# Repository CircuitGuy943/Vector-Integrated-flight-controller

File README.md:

I am currently trying to build my own drone from scratch, and slowly replace every component with my own, from creating fully custom PCBs for the flight controller or ESCs, to making a 3D printed drone chassis etc etc. And this is the fully fledged, multi functional, cool-looking flight controller. I present to you:

# *SABRE!*

For one of my biggest projects yet I designed a jack of all trades custom flight controller board. It also comes with custom firmware, or if possible compatibility with betaflight or other FC firmware out there. At it's core are two PCBs arranged in a stackup with the "top" and "bottom" sections. The two PCBs connect through the common 2.54mm pitch headers and stack on top of eachother and each serve to provide enough space for all the components and separate the sensitive digital components from the electromagnetic potential of the motor power rails. The bottom board houses E-Fuse protection and an INA226 current monitor to protect the boards, including powered FPV feed with the AT7456E and TX5813, accompanied by four MOSFET powered 12V LED strip channels. The top booard houses a powerful STM32F765VGT CPU which will, *fingers crossed,* be more than enough to run automatic flight levelling software quickly enough to not crash. Followed by a micro SD card slot for storing flight telemetry, programmable DIP switched for easy settings, BNO08x 9-DOF sensor module, segment display and pushbuttons for easy configuration without needing to reupload code and a BMP580 barometic sensor. More than I (or you) will ever need to fly a 4 blade, 1KG piece of PETG plastic :)

### Bottom Board:

Half of the bottom PCB houses the power delivery circuitry. This includes a dedicated TPS259850 chip, or an E-Fuse, required protection option for a drone that operates at around 20A sustained and 40A current peaks. Thanks to it's extremely low RDS on, basically no power is wasted, and it trips the circuit in a matter of microseconds when too much current is detected, which makes it extremely useful for a drone full of sensitive circuitry, compared to a traditional wire fuse. Followed by that is an INA226 chip, this aims to precisely monitor the current consumption of the entire drone, helping to predict flight times and efficiently manage battery health, through the use of a shunt resistor sized to the expected current draw. The current planes are optimized to make proper use of the different outer and inner layer thicknesses and properly distribute current with minimal heat up.

The other part of the bottom PCB houses the RF circuitry for the FPV system LED drivers togethor with power regulators that power the 12V rail for the LED drivers and the 5V rail for the FPV system and other 5V chips. The 12V power regulator (TPS55289) and the 5V regulator (TPS63070) both use the safest and most reliable layouts possible and are positioned to spatially divide the high ~32A currents on the bottom power distribution circuitry from the rest of the bottom board, a slide switch also controls the power supply to the TX5813 module, as this consumes the most out of the other board circuitry, at about ~200mA, this should help to increase flight time by cutting wasted power when the FPV function isn't being used. CSD16340 MOSFETS also serve to drive 4 seperate 12V LED strip channels, these I plan to connect to LED strips and create cool illuminations off of my drone.

The RF circuitry benefits from an impedance accurate JLC-3313 stackup and use of coplanar waveguide routing with via fencing, tearsrops and udnerpad via router to insure the least impedance mismatch possible. The actual RF system is composed of an external camera connector, or simple pin header (capable of reading almost any FPV camera such as the Caddx Ant Lite). The video signal is then passed through a meticulously routed 75ohm impedance matched trace into a MAX7456EUI (Or a newer drop in AT7456E replacement, pin to pin compatible), this module serves to inject an OSD (On screen display) into the video feed through communication with the STM32 MCU for easy sending of telemtry data like battery voltage, speed, altitude etc. The output from the OSD injection chip is then routed through another impedance matched trace with SAG correction into the video input of the TX5813. This modules handles the complicated circuitry of converting the video feed (~6MHz) into a radio signal of ~5.8GHz. That RF is then routed even more carefuly for the short length (~8mm) of the SMA launch into the SMA connector then into any respective 5.8GHz FPV antenna. (I also have a complemintary project for a 5.8GHz FPV reciever in another repository)

### Top Board:

Flying the drone is an STM32F765VGT CPU with up to 216MHz clock speed, hopefully resulting in almost perfect drone levelling and flight, on the other side of the board is also a USB C receptacle for programming the STM CPU, and powering the board while doing so (everything except the motors, of course, I also included diodes to prevent power backfeed). Close by is a BNO08x 9-DOF accelerometer, gyroscope and magnetometer, complete with an integrated 32-bit ARM Cortex-M0+ for quick sensor fusion with pre built firmware (meaning I have to code waaaay less :D). Motor PWM outputs for the ESCs also connected directly to PWM channels on the STM32 and two solder bridgeable connections to allow me to use the 5V supply from the ESCs in case my 5V regulator doesn't function properly under load (I've had bad experience with voltage regulators). Several voltage indicator LEDs are also placed near the USB C port at the back. Then there is also an UART FPC port designed to connect to a separate GPS board (large board for good GPS recieving power, check my other repositories) on the left side of the board. A 7 segment, 4 digit bitbanged display and several tactile pushbottoms also occupy the centre of the board, quite useless but they might be useful in changing more accute settings without having to reupload firmware every time. A micro SD card also connects through 4 channel SPI to STM32, I plan to use this to store settings or flight telemetry information that I could analyze while debugging. Powering all that is a 3.3V regulator (LMR51430XF), simplest (and therefore most reliable) I could find. And several other breakout headers for power/functionality. PWM inputs from the radio remote is recieved through a 3x8 header pinout designed for my specific radio reciever module.

(For BP reviewer: Btw, the two boards will be connected and bought as one piece from JLC, then I will cut them apart and stack them, I just ran out of time to do that, there's also quite a bit off polishing off to do like doing Fusion renders but I've also run out of time, so the project would be a bit more polished and it will be but not before the BP deadline. 3D file of board is also too big (over 100MB) to upload to GitHub)

## Features:
- Fully integrated design:
	- Custom firmware uploadable
	- Power distribution and control in one place
	- Dual stacked PCB design
 	- No screw, no wire inter board connection

- Power
	- Extremely low RDS protection e-Fuse (us trip time)
 	- INA226 current and voltage monitoring
  	- Backup/calibration voltage divider monitoring
  	- Fully optimized current planes, 40A+ capability
  	- Firmware built in battery management and flight warning system
  	- Meticulously designed 5V, 12V and 3.3V switching voltage regulators
  	- Backup ESC 5V supply availible
  	- LED indicators for power rail status
  	- 4 channel driver for 12V LED strips
  	- Power switch for TX5813 module for longer flight times

- Fully integrated FPV support
	- MAX7456/AT7456E OSD injection into FPV feed
	- Channel switch ability
	- TX5813 RF launch module
	- Accurate and reliable RF design
 	- Designed for impedance matched JLC 3313 stackup
 
- Flight Control
	- USB C programming connection 
	- Powerful STM32F765VGT CPU
 	- MicroSD card slot (For inflight telemtry storage)
  	- Programmable DIP switches
  	- Display/pushbuttons for setting adjustment without code reupload
  	- BNO08x 9-DOF sensor module with built in sensor fusion
  	- BMP580 Barometric sensor
  	- UART FPC connection for external GPS board
  	- Extra power and I2C debug headers
  	- 7 input PWM channels
  	- 4 ESC output PWM channels

## PCB
This is the PCB, with L1 to L4 Layers, silkscreen for both layers and an all layers view

And here is the schematic

## 3D render
Here is also a 3D render to show off the PCB :)

## Firmware Overview
I've included some basic firmware (**untested**) that should get the TFT display working out of the box with a quick upload from arduino IDE

## BOM:
The BOM list for the actual PCB components is in the BOM folder section and here is also a BOM list for all the other components I plan to buy for this:

- PCB             $378.08		
- Antenna         $7.77      https://www.aliexpress.com/item/1005006153683653.html		
- 90 degree SMA   $4.51      https://www.aliexpress.com/item/1005005665998117.html						
- TX5813 module   $15.82     https://www.aliexpress.com/item/1005011698073364.html
											
Total			      $406.18

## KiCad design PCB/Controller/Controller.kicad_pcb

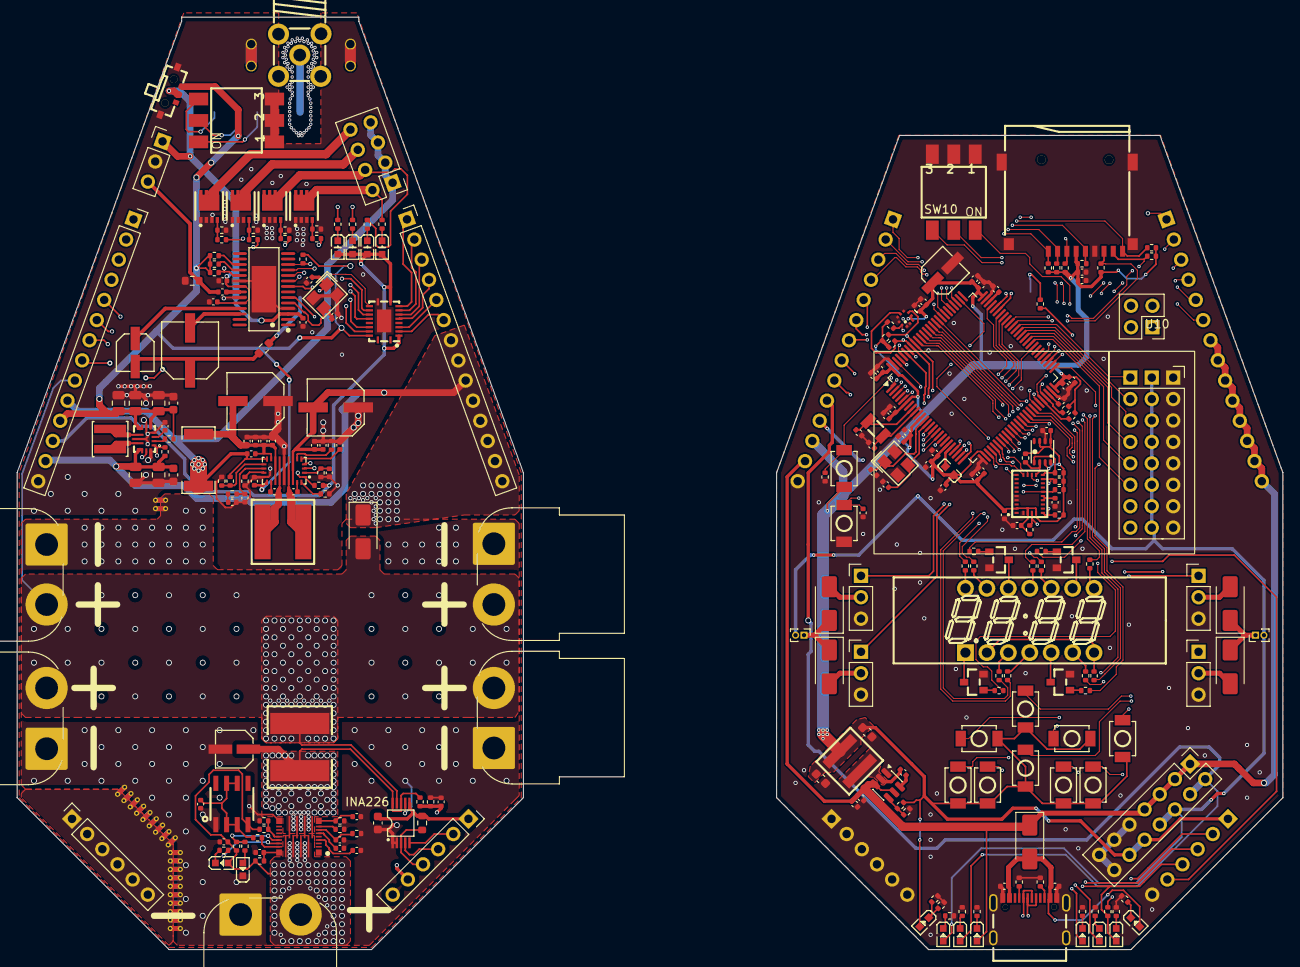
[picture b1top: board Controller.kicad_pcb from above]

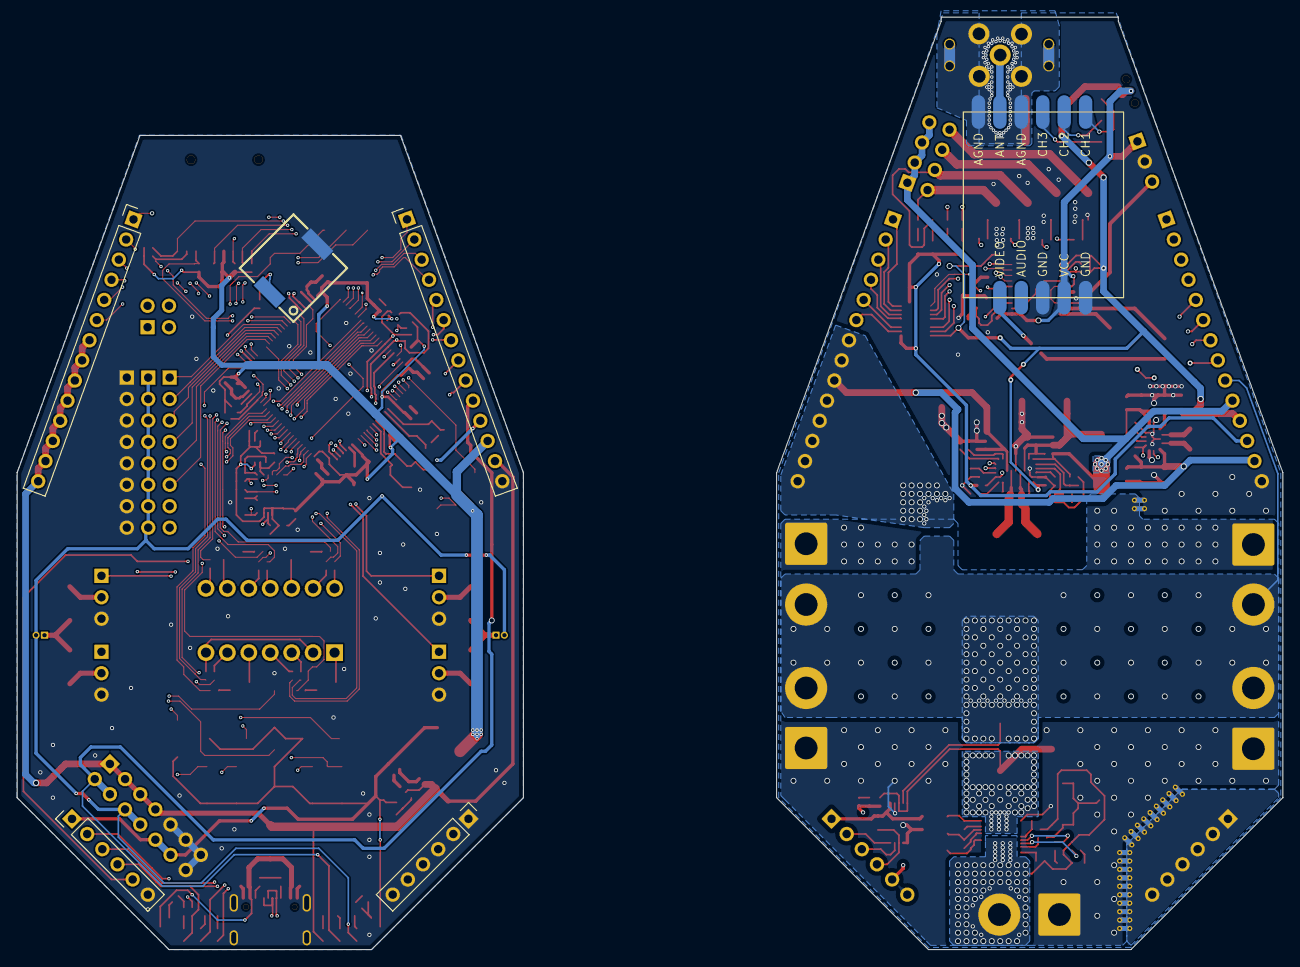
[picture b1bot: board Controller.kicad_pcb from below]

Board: 4 copper layers, 150.0 x 110.5 mm, 284 parts (6 on the bottom side), 219 nets.

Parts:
BUZ1: CPT-9019S-SMT-TR; BUZ-SMD_L9.0-W9.0-P8.00-LS9.3
C1: 0.1uF; C_0603_1608Metric
C2, C11, C14, C15, C26, C27, C29, C30, C31, C32, C33, C34, C36, C37, C38, C41, C44, C45, C46, C47, C48, C49, C50, C51, C63, C64, C67, C78: 100nF; C_0402_1005Metric
C3, C6: 10uF; C_0603_1608Metric
C4, C5: 10uF; C_0805_2012Metric
C7, C8, C9: 22uF; C_0805_2012Metric
C10, C57, C58: 2.2uF; C_0402_1005Metric
C12, C13: 22uF; C_0603_1608Metric
C16, C19, C20, C21, C22: 22uF; C_0402_1005Metric
C17: 4.7uF; C_0402_1005Metric
C18, C28: 22nF; C_0402_1005Metric
C23: 3300pF; C_0402_1005Metric
C24: 330pF; C_0402_1005Metric
C25: 47uF; CAP-SMD_BD6.3-L6.6-W6.6-LS7.2-FD
C35, C43, C56, C68, C77: 10uF; C_0402_1005Metric
C39, C40, C60, C61: 20pF; C_0402_1005Metric
C42, C66, C74: RVT1C220M0405_C3356_22uF; CAP-SMD_BD4.0-L4.3-W4.3-FD-LS5.3
C52, C53, C54, C55, C65: 1uF; C_0402_1005Metric
C59, C62: 6.8pF; C_0402_1005Metric
C69, C75, C76: 0.1uF; C_0402_1005Metric
C70: 15nF; C_0402_1005Metric
C71: 3.3nF; C_0402_1005Metric
C72: 10nF; C_0402_1005Metric
C73: 150pF; C_0402_1005Metric
CN1: XT60PW_M; AMASS_XT60PW-M_1x02_P7.20mm_Horizontal
CN2, CN4, CN5, CN6: XT60PW_F; AMASS_XT60PW-F_1x02_P7.20mm_Horizontal
Card2: TF-01A; TF-SMD_TF-01A
D1, D2, D3, D4, D5, D6: SS34; D_SMA
J1: Conn_02x07_Odd_Even; PinHeader_2x07_P2.54mm_Vertical
J2, J9: Conn_01x02_Pin; PinHeader_1x02_P1.00mm_Vertical
J5, J6, J7, J8, J10: Conn_01x03_Pin; PinHeader_1x03_P2.54mm_Vertical
J12: Conn_02x02_Top_Bottom; PinHeader_2x02_P2.54mm_Vertical
J13, J18: Conn_01x14_Pin; PinHeader_1x14_P2.54mm_Vertical
J14, J19: Conn_01x06_Pin; PinHeader_1x06_P2.54mm_Vertical
J15, J20: Conn_01x14_Socket; PinSocket_1x14_P2.54mm_Vertical
J16, J17: Conn_01x06_Socket; PinSocket_1x06_P2.54mm_Vertical
J21: Conn_02x04_Odd_Even; PinHeader_2x04_P2.54mm_Vertical
L1: XFL4020-152MEC; IND-SMD_L4.0-W4.0-A
L2: FCM1608KF-601T03; L0603
LED1: FJ2481CH; LED-SEG-TH_14P-L32.2-W10.2-P2.54-S7.62-BL
LED2, LED9, LED11, LED12, LED13, LED14, LED15, LED16: KT-0603YG; LED0603-RD
LED3, LED8: KT-0603R; LED0603-RD
LED4, LED5, LED6, LED7: KT-0603W; LED0603-R-RD_WHITE
NT1, NT7, NT8, NT9, NT10, NT10#2, NT10#3, NT10#4, NT11, NT11#2, NT11#3, NT11#4, NT12, NT13, NT13#2, NT13#3, NT14, NT15, NT15#2, NT15#3, NT16: NetTie_2; NetTie-2_THT_Pad0.3mm
NT2, NT17: NetTie_2; NetTie-2_THT_Pad1.0mm
Q1, Q2, Q3, Q5: CSD16340Q3; VSON-CLIP-8_L3.3-W3.3-P0.65-BL
Q7, Q8, Q9, Q10: LBSS138LT1G; SOT-23_L2.9-W1.3-P1.90-LS2.4-BR
R1, R2: 5.1K; R_0402_1005Metric
R3: HOLR2725D-4W-2MR-1%; R2725
R4, R17, R18, R19, R21, R36, R37, R38, R39, R40, R41, R42, R43, R44, R45, R46, R47, R48, R60, R67, R68, R69, R76, R77, R82: 220; R_0402_1005Metric
R5, R72, R73, R74, R75: 680; R_0402_1005Metric
R6, R7, R12, R20, R22, R27, R28, R29, R30, R31, R34, R35, R49, R58, R61, R62, R63, R64, R65, R66, R88, R96, R97, R98, R102: 10K; R_0402_1005Metric
R8, R9: 100K; R_0402_1005Metric
R10: 22.1K; R_0402_1005Metric
R11, R33: 68K; R_0402_1005Metric
R13, R14: 56K; R_0402_1005Metric
R15: MS122WF100MT4E; R2512
R16, R99, R100, R103, R104: 4.7K; R_0402_1005Metric
R23: 150K; R_0402_1005Metric
R24: 47K; R_0402_1005Metric
R25, R26, R55: 2.2K; R_0402_1005Metric
R32, R54, R85, R86, R87: 1K; R_0402_1005Metric
R50: 160; R_0402_1005Metric
R51: 1.1K; R_0402_1005Metric
R52: 48K; R_0402_1005Metric
R53: 1.5K; R_0402_1005Metric
R56: 50K; R_0402_1005Metric
R78: 100; R_0402_1005Metric
R83, R84: 75; R_0603_1608Metric
R101: 10K; R_0603_1608Metric
SW1, SW2, SW3, SW4, SW5, SW6, SW7, SW8, SW9, SW11, SW12: TS-1088-AR02016; SW-SMD_L3.9-W3.0-P4.45
SW10, SW14: DSIC03LSGET; SW-SMD_DSIC03LSGET
SW13: MK-11C04-G013; SW-SMD_MK-11C04-G013
U1: STM32F765VGTx; LQFP-100_14x14mm_P0.5mm
U2: BNO080; LGA-28_L5.2-W3.8-P0.50-BL-1
U3: BMP580; LGA-10_L2.0-W2.0-P0.50-TL_BMP580
U4: XAL5050-562MEC; IND-SMD_L5.5-W5.3
U5: MAX7456EUI; HTSSOP-28_L9.7-W4.4-P0.65-LS6.4-BL-EP5.5
U6: SMA_Conn; SMA-TH_SMA-KWE_C7498154
U7: TPS55289RYQR; VQFN-21_L5.0-W3.0-P0.50-TL
U8: XAL7070-472MEC; IND-SMD_L7.5-W7.2-1
U9: TPS630701RNMT; VQFN-15_L3.0-W2.5-P0.50-BL
U10: MC7RE
U11: INA226AQDGSRQ1; VSSOP-10_L3.0-W3.0-P0.50-LS4.9-BL
U12: LMR51430; SOT-23-6
U13, U18: 100uF; CAP-SMD_BD6.3-L6.6-W6.6-LS7.2-FD-1
U14: BME280; LGA-8_BME280_BL
U15: S322527M20PF10PPM; CRYSTAL-SMD_4P-L3.2-W2.5-BL
U16: TXB0108RGYR; VQFN-20_L4.5-W3.5-P0.50-BL-EP
U17: TX5813
U19: TPS259850RQPR; QFN-26_L5.0-W4.5_TPS259850RQPR
U20: LD1117D33TR; SO-8_L4.9-W3.9-P1.27-LS6.0-BL
USB1: TYPE-C 16P(073); USB-C-SMD_TYPE-C16PIN_C668624
X1: X322525MOB4SI; CRYSTAL-SMD_4P-L3.2-W2.5-BL
X2: Q13FC1350000400; FC-135R_L3.2-W1.5

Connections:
+3.3V: C12.2, C13.2, C29.1, C30.1, C32.2, C33.2, C34.2, C42.1, C43.1, C45.1, C46.1, C47.1, C48.1, C49.1, C50.1, C51.1, C52.1, C53.1, C54.1, C55.1, C56.1, C64.1, C65.1, C67.1, C68.1, Card2.4 (VDD), J1.10, J1.12, J13.12, J14.1, L2.2, LED16.2 (A), R6.2, R9.2, R25.2, R26.2, R27.1, R58.2, R61.2, R62.2, R63.2, R64.2, R65.2, R66.2, R96.1, R97.1, R98.1, R99.1, R100.1, R102.1, R103.2, R104.2, SW1.2, SW2.2, SW3.2, SW4.2, SW5.2, SW6.2, SW7.2, SW8.2, SW9.2, SW12.1, U1.6 (VBAT), U1.11 (VDD), U1.20 (VREF+), U1.27 (VDD), U1.50 (VDD), U1.75 (VDD), U1.100 (VDD), U2.3 (VDD), U2.5 (PS1), U2.28 (VDDIO), U3.1 (VDDIO), U3.10 (VDD), U4.2, U14.2 (CSB), U14.6 (VDDIO), U14.8 (VDD)
+3.3V_B: C1.2, J15.12, J16.1, LED4.1 (A), LED5.1 (A), LED6.1 (A), LED7.1 (A), R28.1, R101.2, U11.6 (VS+), U16.2 (VCCA), U16.10 (OE)
+5V: J1.6, J1.8, J2.2, J9.2, J13.11, LED15.2 (A), U10.17 (5V), U10.18 (5V), U10.19 (5V), U10.20 (5V), U10.21 (5V), U10.22 (5V), U10.23 (5V), U10.24 (SBUS3)
+5V_B: C6.2, C7.2, C8.2, C9.2, C17.2, J15.11, R8.2, R85.2, R86.2, R87.2, R88.2, SW13.1, U7.18 (VCC), U9.5 (FB), U9.7 (VOUT), U16.19 (VCCB)
+12V: J1.2, J1.4, J13.10, LED14.2 (A)
+12V_B: C26.1, J15.10, J21.1, J21.3, J21.5, J21.7, R11.2, R15.2, U7.13 (ISN)
BMP580_INT: R102.2, U1.96 (PB9), U3.7 (INT)
BNO580_BOOTN: R27.2, U1.34 (PB0), U2.4 (BOOTN)
BNO580_CSN: U1.77 (PA15), U2.18 (H_CSN)
BNO580_INTN: R98.2, U1.33 (PC5), U2.14 (H_INTN)
BNO580_MISO: U1.30 (PA6), U2.20 (H_SDA/H_MISO/TX)
BNO580_MOSI: U1.31 (PA7), U2.17 (SA0/H_MOSI)
BNO580_NRST: R97.2, U1.32 (PC4), U2.11 (NRST)
BNO580_SCLK: U1.29 (PA5), U2.19 (H_SCL/SCK/RX)
BNO580_WAKE: R96.2, U1.35 (PB1), U2.6 (PS0/WAKE)
BOOT: R22.1, SW12.2, U1.94 (BOOT0)
BOOT1: C14.2, U7.8 (SW1), U8.2
BOOT2: C15.2, U7.10 (SW2), U8.1
BUTTON_DECREASE: SW4.1, U1.39 (PE9)
BUTTON_F1: SW6.1, U1.41 (PE11)
BUTTON_F2: SW7.1, U1.42 (PE12)
BUTTON_F3: SW8.1, U1.43 (PE13)
BUTTON_F4: SW9.1, U1.51 (PB12)
BUTTON_INCREASE: SW3.1, U1.38 (PE8)
BUTTON_LEFT: SW1.1, U1.36 (PB2)
BUTTON_OK: SW5.1, U1.40 (PE10)
BUTTON_RIGHT: SW2.1, U1.37 (PE7)
BUZZER: R78.1, U1.53 (PB14)
DIP_1: SW10.6 (B1), U1.52 (PB13)
DIP_2: SW10.5 (B2), U1.54 (PB15)
DIP_3: SW10.4 (B3), U1.55 (PD8)
DISP_A: R41.2, U1.87 (PD6)
DISP_B: R44.2, U1.86 (PD5)
DISP_C: R38.2, U1.85 (PD4)
DISP_D: R39.2, U1.84 (PD3)
DISP_D2D1: R45.2, U1.58 (PD11)
DISP_DIG1: R46.1, U1.91 (PB5)
DISP_DIG2: R48.1, U1.90 (PB4)
DISP_DIG3: R36.1, U1.89 (PB3)
DISP_DIG4: R47.1, U1.88 (PD7)
DISP_DP: R40.2, U1.67 (PA8)
DISP_E: R37.2, U1.72 (PA13)
DISP_F: R42.2, U1.69 (PA10)
DISP_G: R43.2, U1.68 (PA9)
EXTRA_I2C_EN: J12.4, U1.44 (PE14)
EXTRA_I2C_INT: J12.3, U1.45 (PE15)
EXTRA_I2C_SCL: J12.1, R103.1, U1.46 (PB10)
EXTRA_I2C_SDA: J12.2, R104.1, U1.47 (PB11)
GND: BUZ1.2 (-), C10.2, C12.1, C13.1, C29.2, C30.2, C31.1, C32.1, C33.1, C34.1, C35.2, C42.2, C43.2, C45.2, C46.2, C47.2, C48.2, C49.2, C50.2, C51.2, C52.2, C53.2, C54.2, C55.2, C56.2, C57.1, C58.1, C59.2, C60.2, C61.1, C62.2, C63.2, C64.2, C65.2, C67.2, C68.2, C77.2, C78.2, Card2.6 (VSS), Card2.10 (GND), Card2.11 (GND), Card2.12 (GND), Card2.13 (GND), J1.9, J1.11, J1.13, J1.14, J5.3, J6.3, J7.3, J8.3, J13.14, J14.6, J19.1, J19.2, J19.3, J19.4, J19.5, J19.6, Q7.2 (S), Q8.2 (S), Q9.2 (S), Q10.2 (S), R1.2, R2.2, R4.2, R5.2, R10.2, R22.2, R72.2, R73.2, R74.2, R75.2, R76.2, R77.2, R82.2, SW10.1 (A1), SW10.2 (A2), SW10.3 (A3), SW11.1, U1.10 (VSS), U1.19 (VSSA), U1.26 (VSS), U1.49 (VSS), U1.74 (VSS), U1.99 (VSS), U2.2 (GND), U2.25 (GND), U2.26 (XOUT32/CLKSEL1), U3.3 (VSS), U3.5 (SDO), U3.6 (CSB), U3.8 (VSS), U3.9 (VSS), U10.9 (GND), U10.10 (GND), U10.11 (GND), U10.12 (GND), U10.13 (GND), U10.14 (GND), U10.15 (GND), U10.16 (SBUS2), U12.1 (GND), U14.1 (GND), U14.7 (GND), USB1.1 (SHELL), USB1.2 (SHELL), USB1.3 (SHELL), USB1.4 (SHELL), USB1.A1B12 (GND), USB1.B1A12 (GND), X1.2 (GND), X1.4 (GND)
GND_B: C2.2, C3.1, C4.1, C5.1, C6.1, C7.1, C8.1, C9.1, C16.1, C17.1, C18.1, C19.1, C20.1, C21.1, C22.1, C23.1, C24.1, C25.1, C27.1, C36.1, C37.1, C38.1, C39.2, C40.1, C44.2, J10.2, J15.14, J16.6, J17.1, J17.2, J17.3, J17.4, J17.5, J17.6, NT1.1, NT2.2, NT7.1, NT8.1, NT9.1, NT10.1, NT10#2.1, NT10#3.1, NT10#4.1, NT11.1, NT11#2.1, NT11#3.1, NT11#4.1, NT12.1, NT13.1, NT13#2.1, NT13#3.1, NT14.1, NT15.1, NT15#2.1, NT15#3.1, NT16.1, NT17.2, Q1.1 (S), Q1.2 (S), Q1.3 (S), Q2.1 (S), Q2.2 (S), Q2.3 (S), Q3.1 (S), Q3.2 (S), Q3.3 (S), Q5.1 (S), Q5.2 (S), Q5.3 (S), R13.1, R14.2, R16.1, R20.2, R29.1, R30.1, R31.1, R34.1, R35.1, R83.2, SW13.4, SW13.5, SW14.1 (A1), SW14.2 (A2), SW14.3 (A3), U5.4 (DGND), U5.20 (AGND), U5.23 (PGND), U5.29 (EP), U7.9 (PGND), U7.17 (AGND), U9.4 (GND), U9.6 (FB2), U9.10 (PGND), U9.15 (VSEL), U13.1, U15.2 (GND), U15.4 (GND), U16.11 (GND), U16.21 (EP), U17.9 (GND), U17.11 (GND)
HSE_IN: C61.2, U1.12 (PH0), X1.1 (OSC1)
HSE_OUT: C60.1, U1.13 (PH1), X1.3 (OSC2)
INA_ALERT_B: J16.4, R101.1, U11.3 (Alert)
INA_ALERT_T: J14.4, LED3.2 (A), R6.1, U1.95 (PB8)
LED1_POWER: J21.8, Q1.5 (D), Q1.6 (D), Q1.7 (D), Q1.8 (D), R67.2
LED1_PWM_B: J15.1, R17.2
LED1_PWM_T: J13.1, U1.15 (PC0)
LED2_POWER: J21.6, Q2.5 (D), Q2.6 (D), Q2.7 (D), Q2.8 (D), R60.2
LED2_PWM_B: J15.2, R18.2
LED2_PWM_T: J13.2, U1.16 (PC1)
LED3_POWER: J21.4, Q5.5 (D), Q5.6 (D), Q5.7 (D), Q5.8 (D), R68.2
LED3_PWM_B: J15.3, R21.2
LED3_PWM_T: J13.3, U1.17 (PC2)
LED4_POWER: J21.2, Q3.5 (D), Q3.6 (D), Q3.7 (D), Q3.8 (D), R69.2
LED4_PWM_B: J15.4, R19.2
LED4_PWM_T: J13.4, U1.18 (PC3)
LSE_IN: C59.1, U1.8 (PC14), X2.1
LSE_OUT: C62.1, U1.9 (PC15), X2.2
MAIN_SCK_B: J15.6, J16.2, U7.3 (SCL), U11.5 (SCL)
MAIN_SCK_T: J13.6, J14.2, R99.2, U1.92 (PB6), U3.2 (SCK)
MAIN_SDA_B: J15.7, J16.3, U7.4 (SDA), U11.4 (SDA)
MAIN_SDA_T: J13.7, J14.3, R100.2, U1.93 (PB7), U3.4 (SDI)
MAX7456_CS_3.3V_B: J20.4, U16.6 (A5)
MAX7456_CS_3.3V_T: J18.4, U1.3 (PE4)
MAX7456_CS_5V: U5.8 (~CS), U16.15 (B5)
MAX7456_HSYNC_5V: R87.1, U5.18 (~HSYNC)
MAX7456_LOS_3.3V_B: J20.5, U16.4 (A3)
MAX7456_LOS_3.3V_T: J18.5, U1.2 (PE3)
MAX7456_LOS_5V: R86.1, U5.12 (LOS), U16.17 (B3)
MAX7456_RESET_3.3V_B: J20.6, U16.3 (A2)
MAX7456_RESET_3.3V_T: J18.6, U1.98 (PE1)
MAX7456_RESET_5V: R88.1, U5.19 (~RESET), U16.18 (B2)
MAX7456_SCLK_3.3V_B: J20.1, U16.9 (A8)
MAX7456_SCLK_3.3V_T: J18.1, U1.1 (PE2)
MAX7456_SCLK_5V: U5.10 (SCLK), U16.12 (B8)
MAX7456_SDIN_3.3V_B: J20.2, U16.8 (A7)
MAX7456_SDIN_3.3V_T: J18.2, U1.5 (PE6)
MAX7456_SDIN_5V: U5.9 (SDIN), U16.13 (B7)
MAX7456_SDOUT_3.3V_B: J20.3, U16.7 (A6)
MAX7456_SDOUT_3.3V_T: J18.3, U1.4 (PE5)
MAX7456_SDOUT_5V: U5.11 (SDOUT), U16.14 (B6)
MAX7456_VSYNC_5V: R85.1, U5.17 (~VSYNC)
MGND_B: C1.1, C28.1, C69.1, C70.2, C71.2, C72.1, C73.1, C74.2, C75.1, C76.2, CN1.1 (-), CN2.2, CN4.2, CN5.2, CN6.2, LED9.1 (K), NT1.2, NT7.2, NT8.2, NT9.2, NT10.2, NT10#2.2, NT10#3.2, NT10#4.2, NT11.2, NT11#2.2, NT11#3.2, NT11#4.2, NT12.2, NT13.2, NT13#2.2, NT13#3.2, NT14.2, NT15.2, NT15#2.2, NT15#3.2, NT16.2, R24.2, R49.1, R50.1, R51.2, R52.2, U11.1 (A1), U11.2 (A0), U11.7 (GND), U19.14 (GND), U20.1 (ADJ/GND)
MOTOR_PWM1: J5.1, U1.22 (PA0)
MOTOR_PWM2: J6.1, U1.23 (PA1)
MOTOR_PWM3: J7.1, U1.24 (PA2)
MOTOR_PWM4: J8.1, U1.25 (PA3)
unnamed: BUZ1.1 (+), R78.2
unnamed: C24.2, R12.1
unnamed: C66.2, R84.2, U18.1
unnamed: C76.1, R56.1, U20.2 (VOUT), U20.3 (VOUT), U20.6 (VOUT), U20.7 (VOUT)
unnamed: C75.2, CN1.2 (+), LED8.2 (A), R32.2, R33.2, R55.1, U19.23 (VIN), U19.24 (VIN), U19.25 (VIN), U19.26 (VIN), U20.4 (VIN)
unnamed: D3.2 (A), J5.2
unnamed: D3.1 (K), D4.1 (K), J2.1
unnamed: D4.2 (A), J6.2
unnamed: D5.2 (A), J7.2
unnamed: D5.1 (K), D6.1 (K), J9.1
unnamed: D6.2 (A), J8.2
unnamed: LED1.14 (A), R42.1
unnamed: LED1.8 (B), R44.1
unnamed: LED1.6 (C), R38.1
unnamed: LED1.11 (D2D1), R41.1
unnamed: LED1.2 (D), LED1.7 (D), R39.1
unnamed: LED1.1 (DIG1), Q7.3 (D)
unnamed: LED1.12 (DIG2), Q10.3 (D)
unnamed: LED1.5 (DIG3), Q8.3 (D)
unnamed: LED1.9 (DIG4), Q9.3 (D)
unnamed: LED1.3 (DP), R40.1
unnamed: LED1.4 (E), R37.1
unnamed: LED1.13 (F), R45.1
unnamed: LED1.10 (G), R43.1
unnamed: LED2.1 (K), R72.1
unnamed: LED3.1 (K), R4.1
unnamed: LED4.2 (K), R67.1
unnamed: LED5.2 (K), R60.1
unnamed: LED6.2 (K), R68.1
unnamed: LED7.2 (K), R69.1
unnamed: LED8.1 (K), R53.1
unnamed: LED9.2 (A), R54.1
unnamed: LED11.1 (K), R5.1
unnamed: LED12.1 (K), R73.1
unnamed: LED13.1 (K), R74.1
unnamed: LED14.1 (K), R75.1
unnamed: LED15.1 (K), R76.1
unnamed: LED16.1 (K), R77.1, R82.1
unnamed: NT2.1, NT17.1, U6.1, U6.2, U6.3, U6.4, U17.1 (AGND), U17.3 (AGND)
unnamed: Q1.4 (G), R17.1, R29.2
unnamed: Q2.4 (G), R18.1, R30.2
unnamed: Q3.4 (G), R19.1, R34.2
unnamed: Q5.4 (G), R21.1, R31.2
unnamed: Q7.1 (G), R46.2
unnamed: Q8.1 (G), R36.2
unnamed: Q9.1 (G), R47.2
unnamed: Q10.1 (G), R48.2
unnamed: C57.2, U1.48 (VCAP_1)
unnamed: C58.2, U1.73 (VCAP_2)
unnamed: L2.1, U1.21 (VDDA)
unnamed: C31.2, U2.9 (CAP), U2.10 (CLKSEL0)
unnamed: C66.1, U5.25 (SAG)
unnamed: C41.2, U5.22 (VIN)
unnamed: U5.26 (VOUT), U18.2
unnamed: C14.1, U7.20 (BOOT1)
unnamed: C15.1, U7.19 (BOOT2)
unnamed: R13.2, U7.16 (CDC)
unnamed: C23.2, R12.2, U7.15 (COMP)
unnamed: C18.2, U7.5 (DITH/SYNC)
unnamed: R20.1, U7.21 (EXTVCC)
unnamed: R11.1, R16.2, U7.14 (FB/~INT)
unnamed: R14.1, U7.6 (FSW)
unnamed: C19.2, C20.2, C21.2, C22.2, C25.2, C26.2, R15.1, U7.11 (VOUT), U7.12 (ISP)
unnamed: C44.1, R35.2, U7.2 (MODE)
unnamed: R7.2, U9.1 (PS/S), U9.14 (EN)
unnamed: L1.1, U9.11 (L1)
unnamed: L1.2, U9.9 (L2)
unnamed: R8.1, U9.2 (PG)
unnamed: C2.1, U9.3 (VAUX)
unnamed: C11.1, U12.6 (CB)
unnamed: R9.1, R10.1, U12.4 (FB)
unnamed: C11.2, U4.1, U12.2 (SW)
unnamed: R26.1, U2.15 (ENV_SCL), U14.4 (SCK)
unnamed: R25.1, U2.16 (ENV_SDA), U14.3 (SDI)
unnamed: U6.5, U17.2 (ANT)
unnamed: C71.1, U19.4 (DVDT)
unnamed: R33.1, R49.2, U19.18 (EN/UVLO)
unnamed: R50.2, U19.8 (ILIM)
unnamed: C72.2, R51.1, U19.7 (IMON)
unnamed: C73.2, R52.1, U19.9 (IREF)
unnamed: C70.1, U19.6 (ITIMER)
unnamed: R54.2, R55.2, U19.19 (PG)
unnamed: R56.2, U19.21 (SWEN)
unnamed: C69.2, R32.1, U19.22 (VDD)
unnamed: R53.2, U19.20 (~FLT)
unnamed: R2.1, USB1.A5 (CC1)
unnamed: R1.1, USB1.B5 (CC2)
RADIO_PWM1: U1.64 (PC7), U10.1 (CH1)
RADIO_PWM2: U1.63 (PC6), U10.2 (CH2)
RADIO_PWM3: U1.62 (PD15), U10.3 (CH3)
RADIO_PWM4: U1.61 (PD14), U10.4 (CH4)
RADIO_PWM5: U1.60 (PD13), U10.5 (CH5)
RADIO_PWM6: U1.59 (PD12), U10.6 (CH6)
RESET: C63.1, SW11.2, U1.14 (NRST)
SD_CD: Card2.9 (CD), R58.1, U1.82 (PD1)
SD_CLK: Card2.5 (CLK(SCLK)), R64.1, U1.80 (PC12)
SD_CMD: Card2.3 (CMD(DI)), R65.1, U1.83 (PD2)
SD_DAT0: Card2.7 (DAT0(D0)), R63.1, U1.65 (PC8)
SD_DAT1: Card2.8 (DAT1(RSV)), R62.1, U1.66 (PC9)
SD_DAT2: Card2.1 (DAT2(RSV)), R61.1, U1.78 (PC10)
SD_DAT3: Card2.2 (CDDAT3(CS)), R66.1, U1.79 (PC11)
TPS_ENABLE_B: J15.5, R28.2, U7.1 (EN/UVLO)
TPS_ENABLE_T: J13.5, U1.97 (PE0)
USB_DN: U1.70 (PA11), USB1.A7 (DN1), USB1.B7 (DN2)
USB_DP: U1.71 (PA12), USB1.A6 (DP1), USB1.B6 (DP2)
VBAT: J13.8, LED11.2 (A)
VBAT_B: C74.1, J15.8, R3.2, R23.1, U11.8 (VBUS), U11.10 (VIN+), U19.10 (VOUT), U19.11 (VOUT), U19.12 (VOUT), U19.13 (VOUT)
VBUS: C35.1, C77.1, D1.2 (A), LED2.2 (A), USB1.A4B9 (VBUS), USB1.B4A9 (VBUS)
VIDEO_IN: C41.1, J10.3, R83.1
VIDEO_OUT: R84.1, U17.7 (VIDEO)
VMOTORS: J13.9, LED12.2 (A)
VMOTORS_B: CN2.1, CN4.1, CN5.1, CN6.1, D2.2 (A), J15.9, R3.1, U11.9 (VIN-)
VOLTAGE_ADC_B: C28.2, J16.5, R23.2, R24.1
VOLTAGE_ADC_T: J14.5, U1.28 (PA4)
VSYS: C10.1, C78.1, D1.1 (K), J1.1, J1.3, J1.5, J1.7, J13.13, J18.7, J18.8, J18.9, J18.10, J18.11, J18.12, J18.13, J18.14, LED13.2 (A), U12.3 (VIN), U12.5 (EN)
VSYS_B: C3.2, C4.2, C5.2, C16.2, C27.2, D2.1 (K), J15.13, J20.7, J20.8, J20.9, J20.10, J20.11, J20.12, J20.13, J20.14, R7.1, U7.7 (VIN), U9.12 (VIN), U13.2
VTX_CH1: SW14.4 (B3), U17.6 (CH1)
VTX_CH2: SW14.5 (B2), U17.5 (CH2)
VTX_CH3: SW14.6 (B1), U17.4 (CH3)
VTX_SUPPLY: C36.2, C37.2, C38.2, J10.1, SW13.C, U5.3 (DVDD), U5.21 (AVDD), U5.24 (PVDD), U17.10 (VCC)
XTAL1: C40.2, U5.5 (CLKIN), U15.3
XTAL2: C39.1, U5.6 (XFB), U15.1

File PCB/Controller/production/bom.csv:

Designator,Footprint,Quantity,Value,LCSC Part #
BUZ1,BUZ-SMD_L9.0-W9.0-P8.00-LS9.3,1,CPT-9019S-SMT-TR,C95163
C1,0603,1,0.1uF,
"C10, C57, C58",0402,3,2.2uF,
"C11, C14, C15, C2, C27, C29, C30, C31, C32, C33, C34, C36, C37, C38, C41, C44, C45, C46, C47, C48, C49, C50, C51, C63, C64, C67, C78",0402,27,100nF,
"C12, C13",0603,2,22uF,
"C16, C19, C20, C21, C22",0402,5,22uF,
C17,0402,1,4.7uF,
"C18, C28",0402,2,22nF,
C23,0402,1,3300pF,
C24,0402,1,330pF,
C25,CAP-SMD_BD6.3-L6.6-W6.6-LS7.2-FD,1,47uF,C970677
"C3, C6",0603,2,10uF,
"C35, C43, C56, C68, C77",0402,5,10uF,
"C39, C40, C60, C61",0402,4,20pF,
"C4, C5",0805,2,10uF,
"C42, C74",CAP-SMD_BD4.0-L4.3-W4.3-FD-LS5.3,2,RVT1C220M0405_C3356_22uF,C3356
"C52, C53, C54, C55, C65",0402,5,1uF,
"C59, C62",0402,2,6.8pF,
C66,1210,1,100uF,
"C69, C75, C76",0402,3,0.1uF,
"C7, C8, C9",0805,3,22uF,
C70,0402,1,15nF,
C71,0402,1,3.3nF,
C72,0402,1,10nF,
C73,0402,1,150pF,
C79,1206,1,22uF,
CARD2,TF-SMD_TF-01A,1,TF-01A,C91145
CN1,AMASS_XT60PW-M_1x02_P7.20mm_Horizontal,1,XT60PW_M,C98732
"CN2, CN4, CN5, CN6",AMASS_XT60PW-F_1x02_P7.20mm_Horizontal,4,XT60PW_F,C428722
"D1, D2, D3, D4, D5, D6",D_SMA,6,SS34,
GPS,FPC-SMD_6P-P0.50_XUNPU_FPC-05F-6PH20,1,FPC-05F-6PH20,C2856796
J1,PinHeader_2x07_P2.54mm_Vertical,1,Conn_02x07_Odd_Even,
"J10, J5, J6, J7, J8",PinHeader_1x03_P2.54mm_Vertical,5,Conn_01x03_Pin,
J12,PinHeader_2x02_P2.54mm_Vertical,1,Conn_02x02_Top_Bottom,
"J13, J18",PinHeader_1x14_P2.54mm_Vertical,2,Conn_01x14_Pin,
"J14, J19",PinHeader_1x06_P2.54mm_Vertical,2,Conn_01x06_Pin,
"J15, J20",PinSocket_1x14_P2.54mm_Vertical,2,Conn_01x14_Socket,
"J16, J17",PinSocket_1x06_P2.54mm_Vertical,2,Conn_01x06_Socket,
"J2, J9",PinHeader_1x02_P1.00mm_Vertical,2,Conn_01x02_Pin,
J21,PinHeader_2x04_P2.54mm_Vertical,1,Conn_02x04_Odd_Even,
L1,IND-SMD_L4.0-W4.0-A,1,XFL4020-152MEC,C3033018
L2,L0603,1,FCM1608KF-601T03,C141723
LED1,LED-SEG-TH_14P-L32.2-W10.2-P2.54-S7.62-BL,1,FJ2481CH,C10707
"LED11, LED12, LED13, LED14, LED15, LED16, LED2, LED9",LED0603-RD,8,KT-0603YG,C2289
"LED3, LED8",LED0603-RD,2,KT-0603R,C2286
"LED4, LED5, LED6, LED7",LED0603-R-RD_WHITE,4,KT-0603W,C2290
"Q1, Q2, Q3, Q5",VSON-CLIP-8_L3.3-W3.3-P0.65-BL,4,CSD16340Q3,C47616
"Q10, Q7, Q8, Q9",SOT-23_L2.9-W1.3-P1.90-LS2.4-BR,4,LBSS138LT1G,C8490
"R1, R2",0402,2,5.1K,
R10,0402,1,22.1K,
"R100, R103, R104, R16, R99",0402,5,4.7K,
R101,0603,1,10K,
"R102, R12, R20, R22, R27, R28, R29, R30, R31, R34, R35, R49, R58, R6, R61, R62, R63, R64, R65, R66, R7, R88, R96, R97, R98",0402,25,10K,
"R11, R33",0402,2,68K,
"R13, R14",0402,2,56K,
"R15, R52",0402,2,24K,
"R17, R18, R19, R21, R36, R37, R38, R39, R4, R40, R41, R42, R43, R44, R45, R46, R47, R48, R60, R67, R68, R69, R76, R77, R82",0402,25,220,
R23,0402,1,150K,
R24,0402,1,47K,
"R25, R26, R55",0402,3,2.2K,
R3,R2725,1,HOLR2725D-4W-2MR-1%,C500746
"R32, R54, R85, R86, R87",0402,5,1K,
"R5, R72, R73, R74, R75",0402,5,680,
R50,0402,1,160,
R51,0402,1,1.1K,
R53,0402,1,1.5K,
R56,0402,1,50K,
R78,0402,1,100,
"R8, R9",0402,2,100K,
"R83, R84",0603,2,75,
"SW1, SW11, SW12, SW2, SW3, SW4, SW5, SW6, SW7, SW8, SW9",SW-SMD_L3.9-W3.0-P4.45,11,TS-1088-AR02016,C720477
"SW10, SW14",SW-SMD_DSIC03LSGET,2,DSIC03LSGET,C57453
SW13,SW-SMD_MK-11C04-G013,1,MK-11C04-G013,C778185
U1,LQFP-100_14x14mm_P0.5mm,1,STM32F765VGTx,
U10,MC7RE,1,~,
U11,VSSOP-10_L3.0-W3.0-P0.50-LS4.9-BL,1,INA226AQDGSRQ1,C2653835
U12,SOT-23-6,1,LMR51430XF,
U13,CAP-SMD_BD6.3-L6.6-W6.6-LS7.2-FD-1,1,100uF,C970685
U14,LGA-8_BME280_BL,1,BME280,C92489
U15,CRYSTAL-SMD_4P-L3.2-W2.5-BL,1,S322527M20PF10PPM,C7420779
U16,VQFN-20_L4.5-W3.5-P0.50-BL-EP,1,TXB0108RGYR,C194701
U17,TX5813,1,TX5813,
U19,QFN-26_L5.0-W4.5_TPS259850RQPR,1,TPS259850RQPR,C6290347
U2,LGA-28_L5.2-W3.8-P0.50-BL-1,1,BNO080,C717991
U20,SO-8_L4.9-W3.9-P1.27-LS6.0-BL,1,LD1117D33TR,C2971297
U3,LGA-10_L2.0-W2.0-P0.50-TL_BMP580,1,BMP580,C22391138
U4,IND-SMD_L5.5-W5.3,1,XAL5050-562MEC,C7305309
U5,HTSSOP-28_L9.7-W4.4-P0.65-LS6.4-BL-EP5.5,1,MAX7456EUI,C5346361
U6,SMA-TH_SMA-KWE_C7498154,1,SMA_Conn,C7498154
U7,VQFN-21_L5.0-W3.0-P0.50-TL,1,TPS55289RYQR,C5942077
U8,IND-SMD_L7.5-W7.2-1,1,XAL7070-472MEC,C3911513
U9,VQFN-15_L3.0-W2.5-P0.50-BL,1,TPS630701RNMT,C181473
USB1,USB-C-SMD_TYPE-C16PIN_C668624,1,TYPE-C 16P(073),C668624
X1,CRYSTAL-SMD_4P-L3.2-W2.5-BL,1,X322525MOB4SI,C9006
X2,FC-135R_L3.2-W1.5,1,Q13FC1350000400,C32346

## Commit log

2025-12-31 Add PCB Files
2026-01-02 Create LICENSE
2026-03-30 Enhance README with additional image and project details
    Added an additional image and expanded project description for the custom flight controller board, detailing its features and components.
